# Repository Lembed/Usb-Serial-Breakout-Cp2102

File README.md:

# Usb-Serial-Breakout

usb to serial converter base on cp2102

##License
[MIT](https://github.com/Lembed/Usb-Serial-Breakout/blob/master/LICENSE)

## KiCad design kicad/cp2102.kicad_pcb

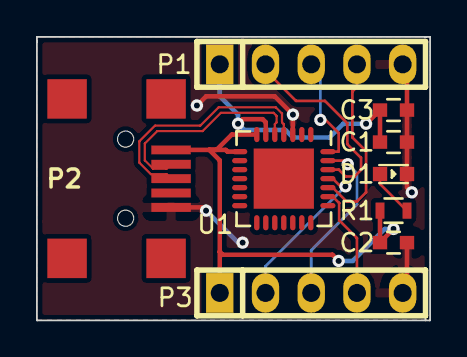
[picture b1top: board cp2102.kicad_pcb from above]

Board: 2 copper layers, 21.8 x 15.7 mm, 10 parts (1 on the bottom side), 12 nets.

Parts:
C1: 10uf; CAP_0603
C2: 1uf; CAP_0603
C3: 0.1uf; CAP_0603
D1: LED; LED-0603
LOGO1: LEMBED-LOGO; LOGO_LEMBED
P1, P3: CONN_01X05; PIN_SOCKET_5
P2: MICRO-USB-B; USB_B_MINI_SMD
R1: 330; R_0603
U1: CP2102; QFN-28-1EP_5x5mm_Pitch0.5mm

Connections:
+3V3: C1.1, C3.1, P1.1, U1.6
/CTS: P3.4, U1.23
/D+: P2.3, U1.4
/D-: P2.2, U1.5
/DSR: P3.3, U1.27
/DTR: P1.3, U1.28
/RTS: P1.4, U1.24
/RXD: P3.2, U1.25
/TXD: P1.2, U1.26
GND: C1.2, C2.2, C3.2, D1.2, P1.5, P2.5, P3.5, U1.3
unnamed: D1.1, R1.2
VCC: C2.1, P2.1, P3.1, R1.1, U1.7, U1.8

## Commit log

2016-04-25 update hardware
2016-05-13 move to kicad dir
2016-05-14 add gerber
2016-09-17 ver2.0
2016-09-17 fix library path
